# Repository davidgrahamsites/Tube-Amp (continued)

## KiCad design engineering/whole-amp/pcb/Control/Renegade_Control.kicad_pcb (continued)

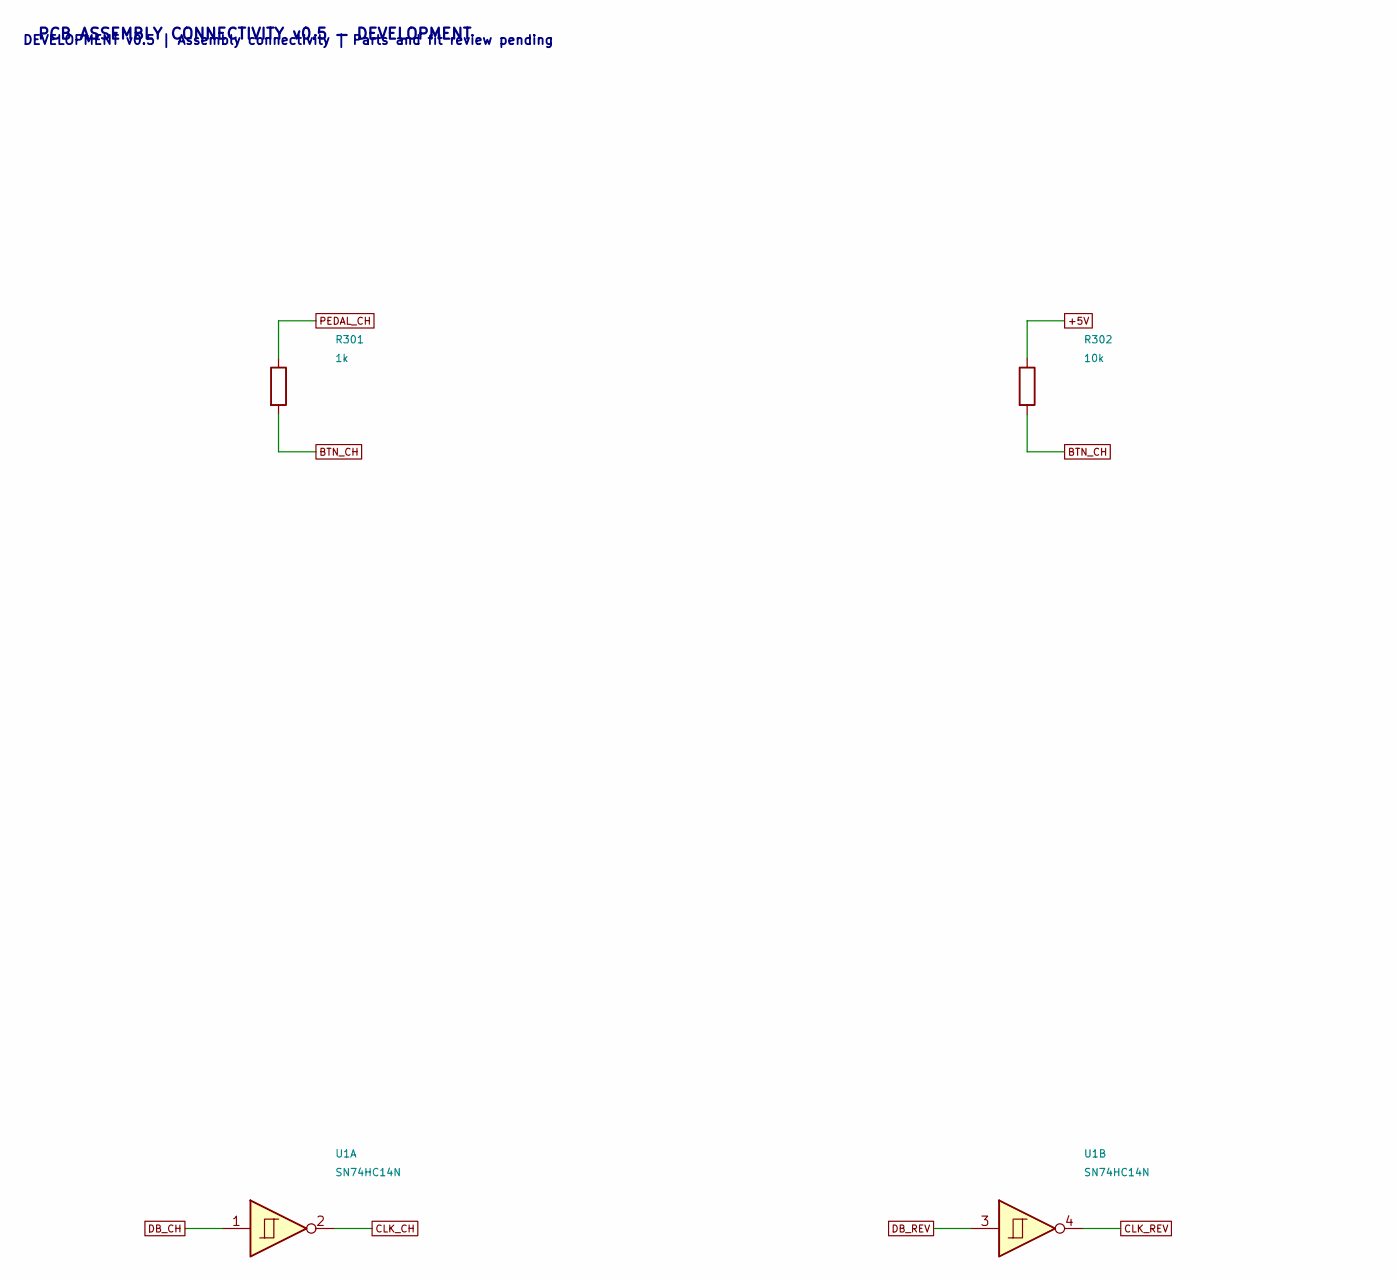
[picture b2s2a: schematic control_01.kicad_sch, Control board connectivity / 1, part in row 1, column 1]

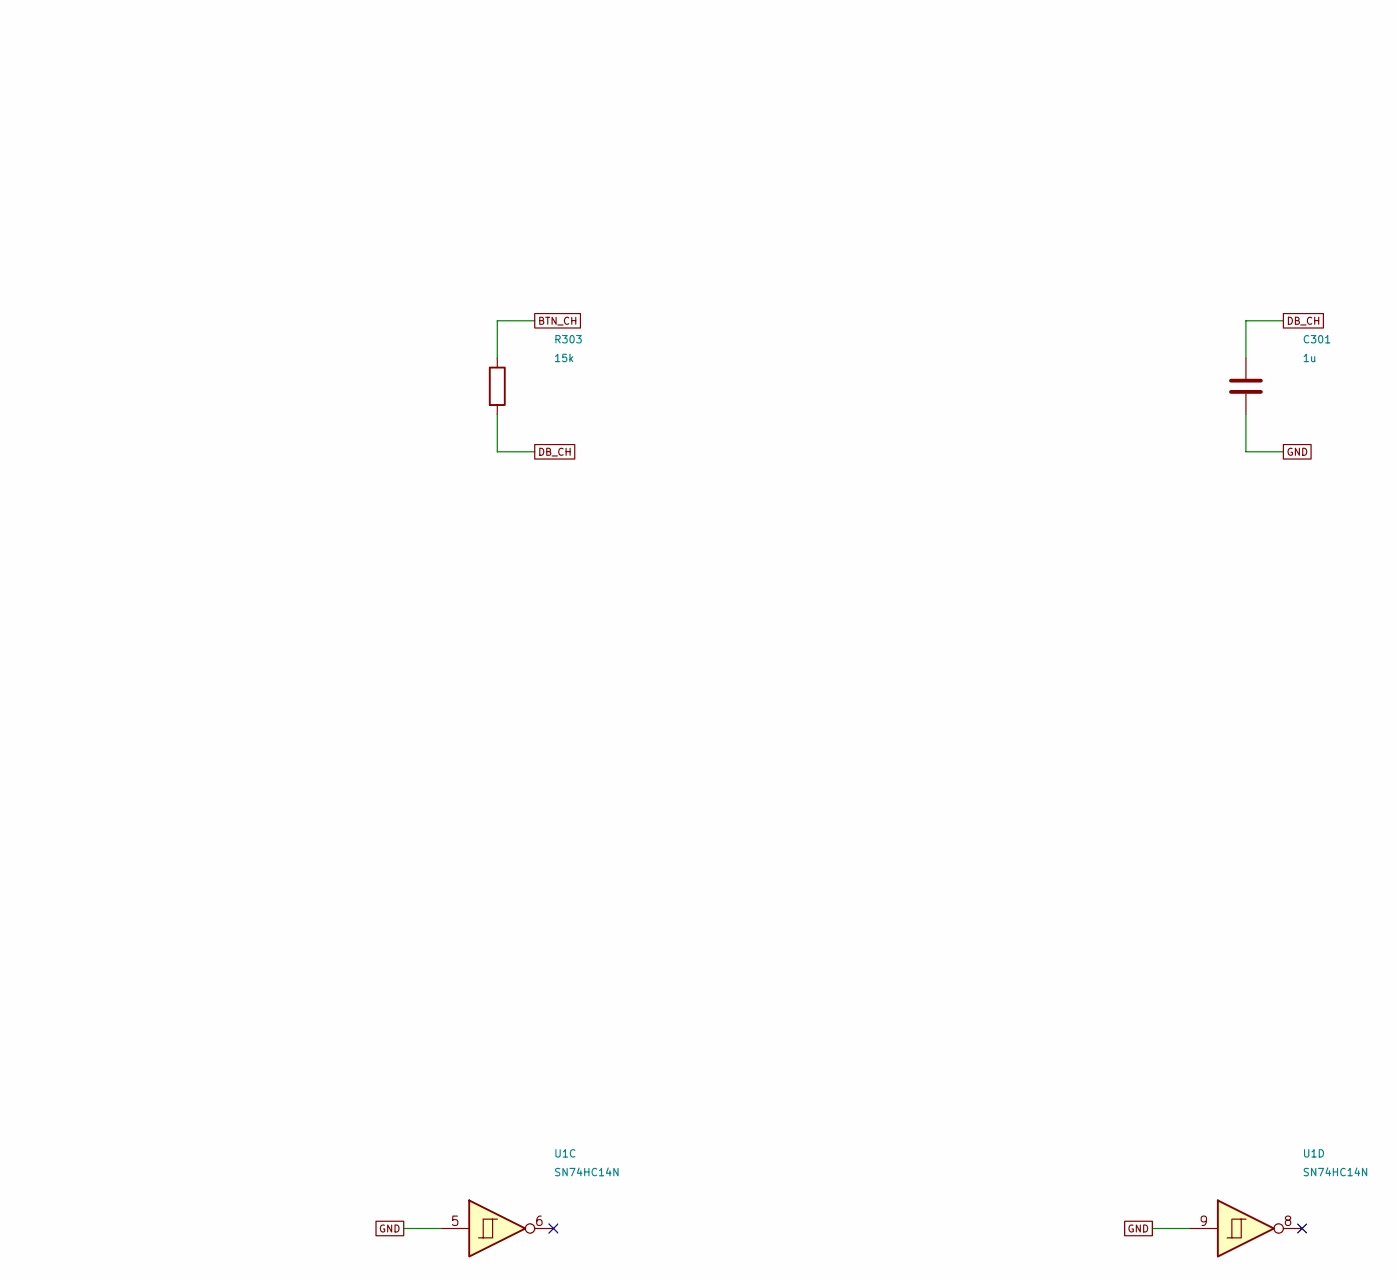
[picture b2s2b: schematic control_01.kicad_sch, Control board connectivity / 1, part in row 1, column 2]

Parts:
C301: 1u; CP_Radial_D8.0mm_P3.50mm; Rating 16 V; effective capacitance/tolerance p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
R301: 1k; R_Axial_DIN0207_L6.3mm_D2.5mm_P10.16mm_Horizontal; Rating 0.25 W; cable current limiter
R302: 10k; R_Axial_DIN0207_L6.3mm_D2.5mm_P10.16mm_Horizontal; Rating 0.25 W
R303: 15k; R_Axial_DIN0207_L6.3mm_D2.5mm_P10.16mm_Horizontal; Rating 1% 0.25 W
U1: SN74HC14N; DIP-14_W7.62mm

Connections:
+5V: R302.1; also elsewhere on the board
BTN_CH: R301.2, R302.2, R303.1; also elsewhere on the board
CLK_CH: U1.2; also elsewhere on the board
CLK_REV: U1.4; also elsewhere on the board
DB_CH: C301.1, R303.2, U1.1
DB_REV: U1.3; also elsewhere on the board
GND: C301.2, U1.5, U1.9; also elsewhere on the board
PEDAL_CH: R301.1; also elsewhere on the board

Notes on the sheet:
PCB ASSEMBLY CONNECTIVITY v0.5 — DEVELOPMENT
DEVELOPMENT v0.5 | Assembly connectivity | Parts and fit review pending

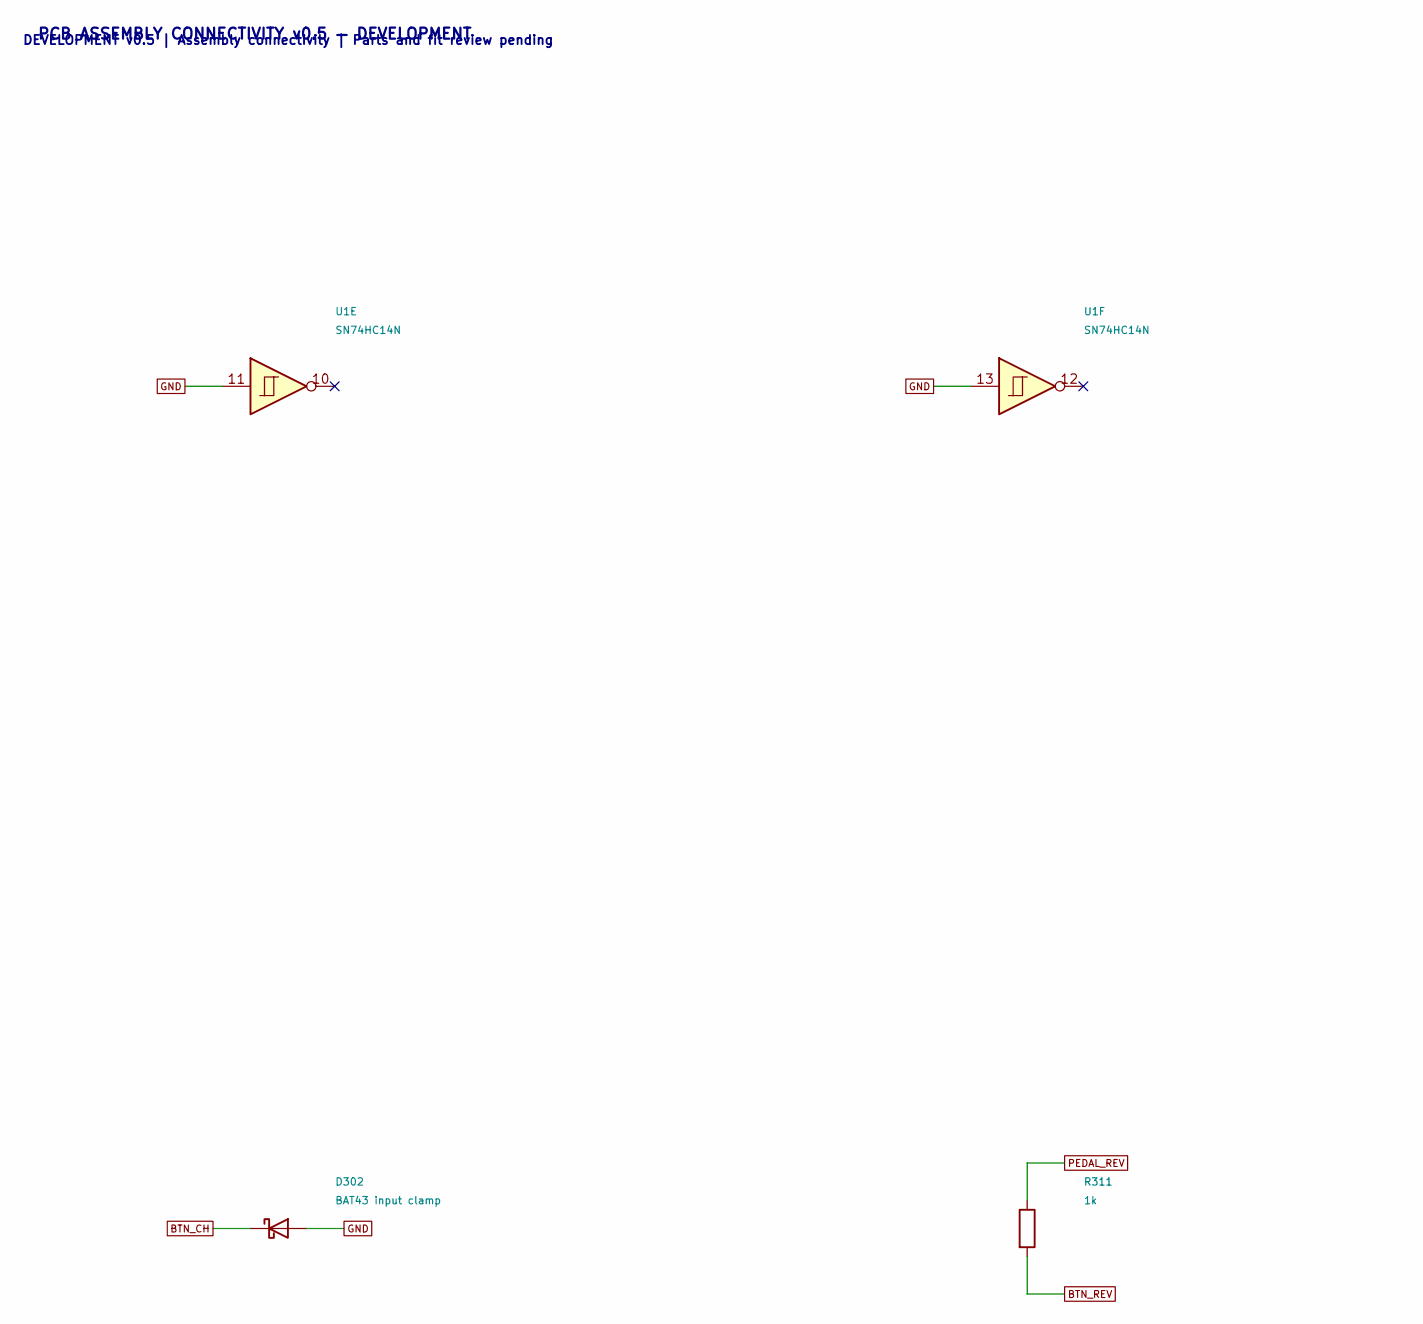
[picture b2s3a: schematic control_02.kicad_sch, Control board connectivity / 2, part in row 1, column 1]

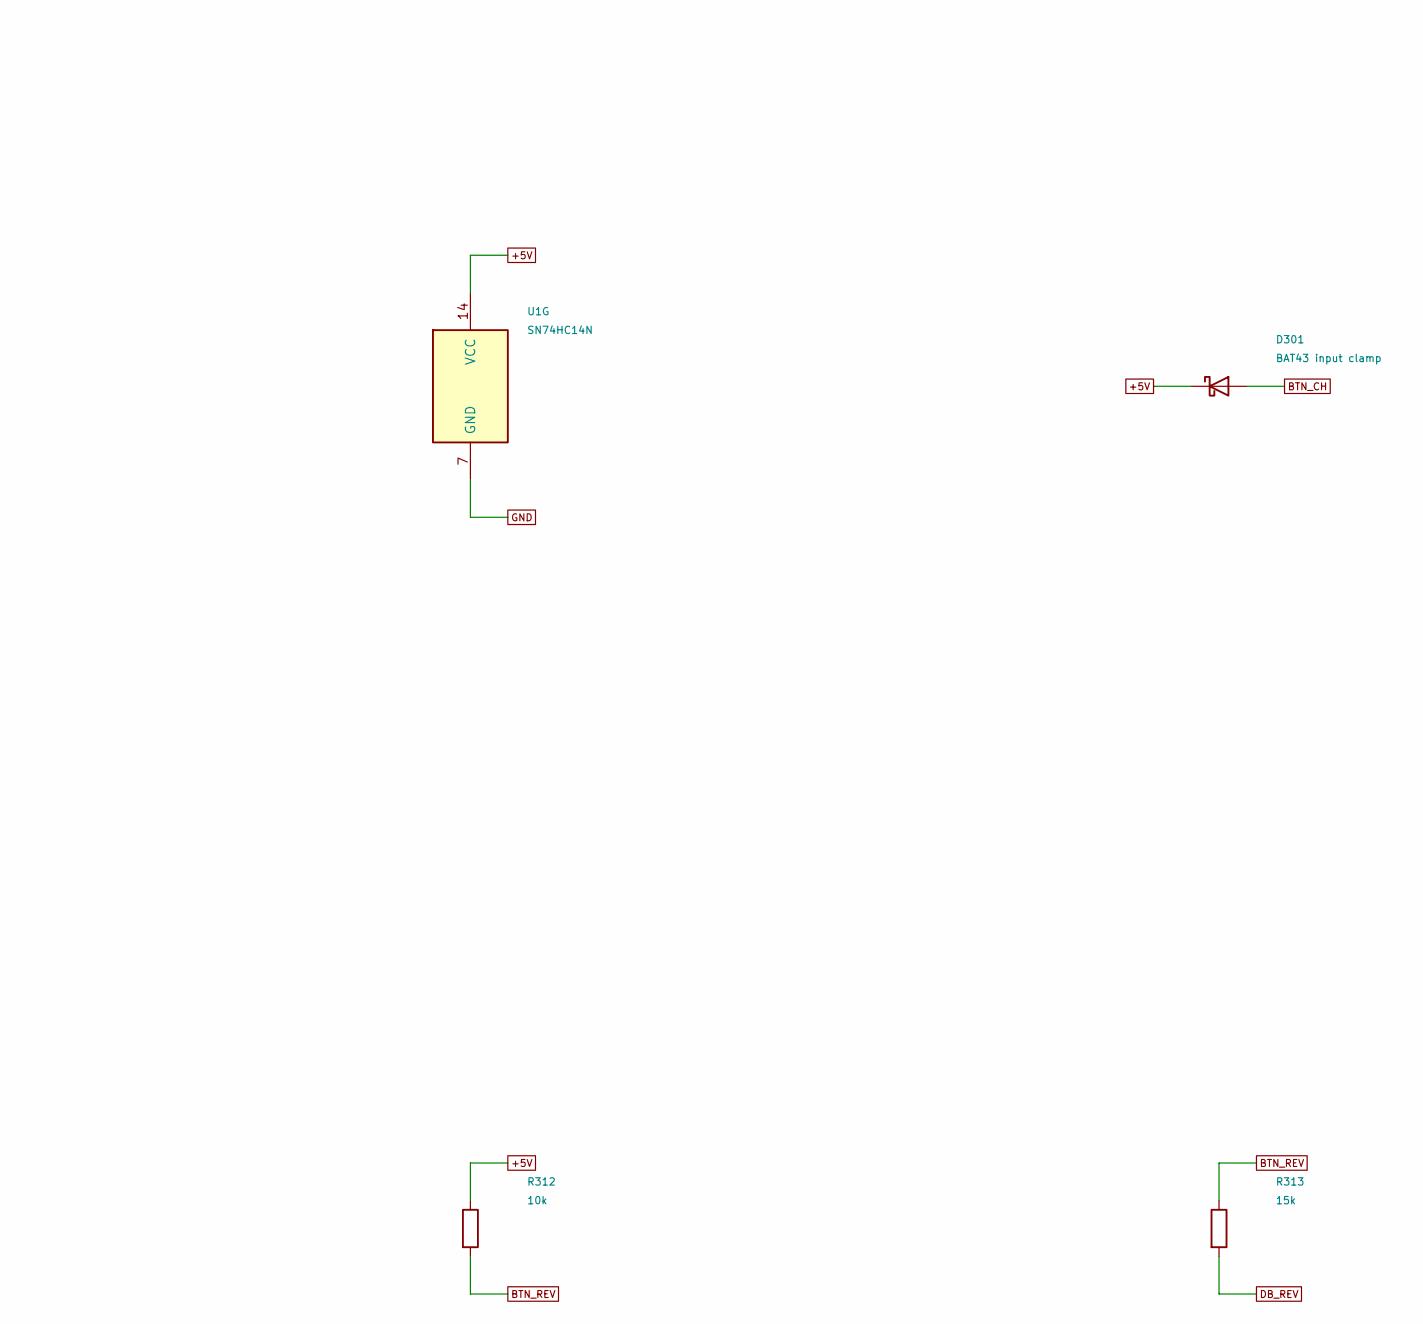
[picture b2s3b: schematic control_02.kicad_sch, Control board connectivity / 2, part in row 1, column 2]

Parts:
D301, D302: BAT43 input clamp; D_DO-35_SOD27_P10.16mm_Horizontal; Rating ESD TVS/connector shell termination sti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
R311: 1k; R_Axial_DIN0207_L6.3mm_D2.5mm_P10.16mm_Horizontal; Rating 0.25 W; cable current limiter
R312: 10k; R_Axial_DIN0207_L6.3mm_D2.5mm_P10.16mm_Horizontal; Rating 0.25 W
R313: 15k; R_Axial_DIN0207_L6.3mm_D2.5mm_P10.16mm_Horizontal; Rating 1% 0.25 W
U1: SN74HC14N; DIP-14_W7.62mm

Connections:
+5V: D301.1 (K), R312.1, U1.14 (VCC); also elsewhere on the board
BTN_CH: D301.2 (A), D302.1 (K); also elsewhere on the board
BTN_REV: R311.2, R312.2, R313.1; also elsewhere on the board
DB_REV: R313.2; also elsewhere on the board
GND: D302.2 (A), U1.7 (GND), U1.11, U1.13; also elsewhere on the board
PEDAL_REV: R311.1; also elsewhere on the board

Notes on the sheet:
PCB ASSEMBLY CONNECTIVITY v0.5 — DEVELOPMENT
DEVELOPMENT v0.5 | Assembly connectivity | Parts and fit review pending

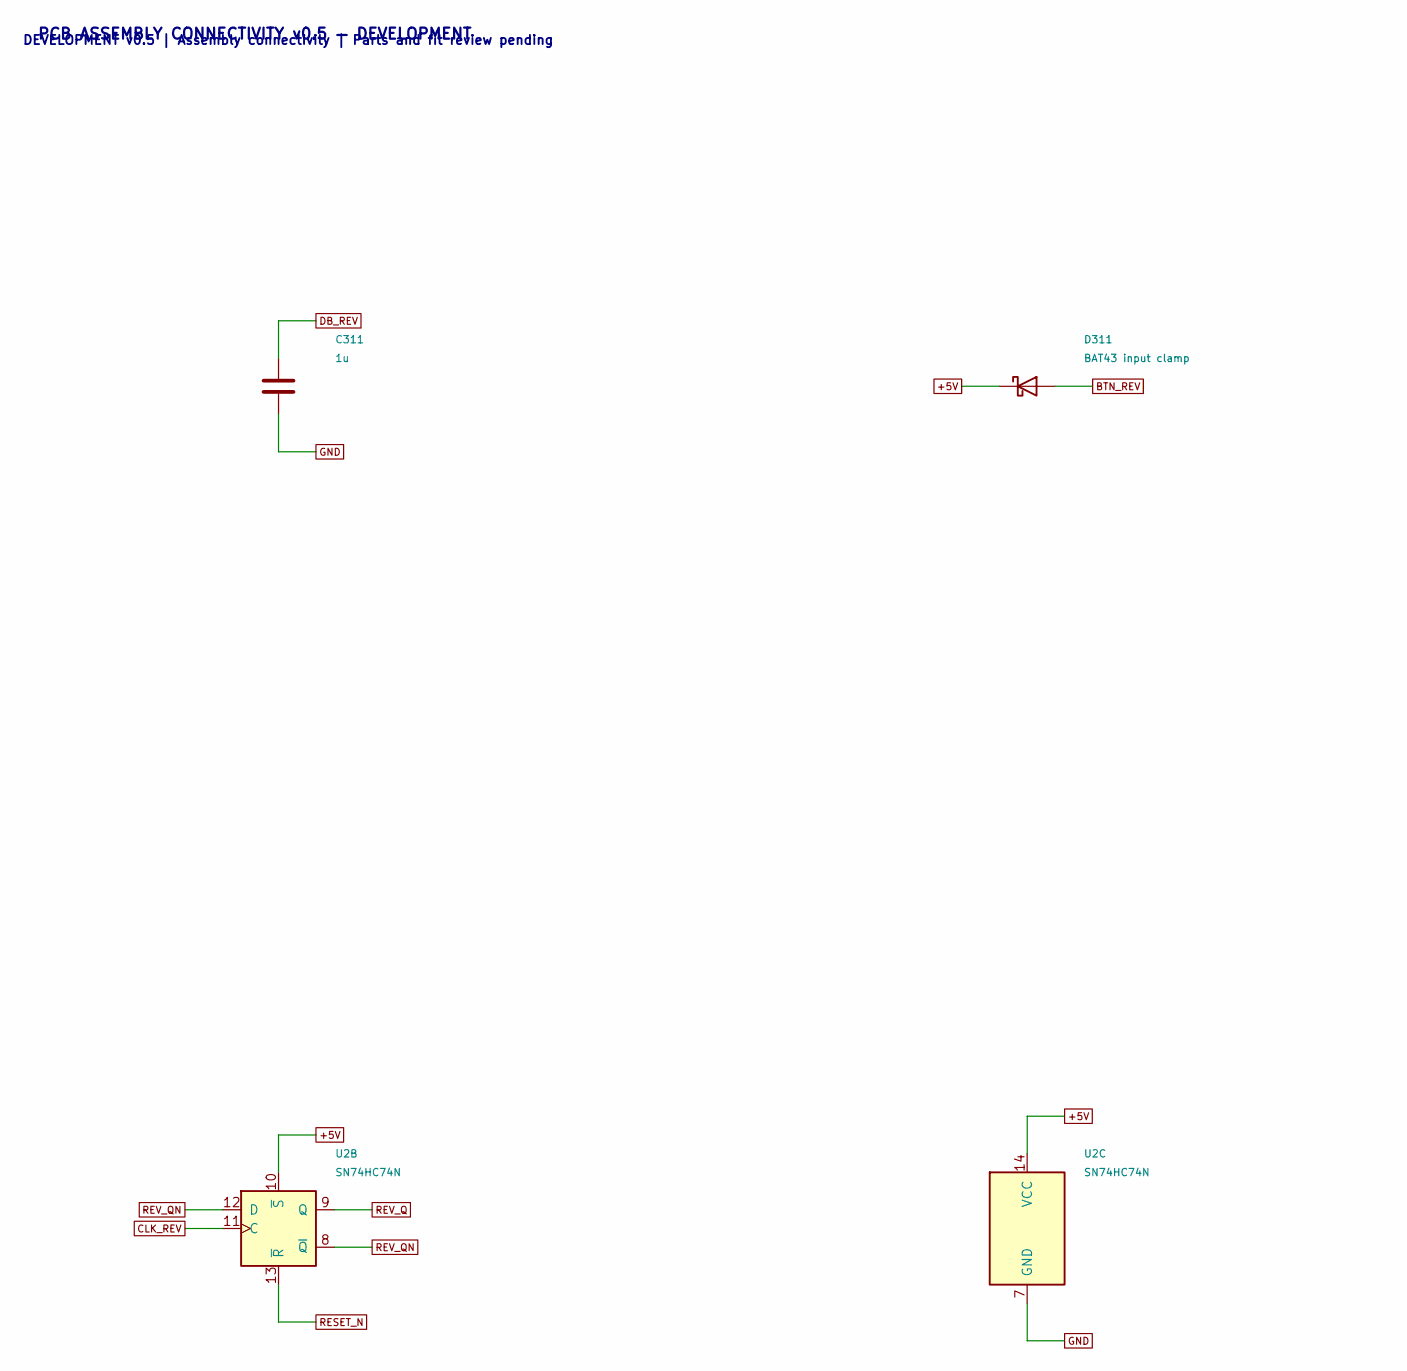
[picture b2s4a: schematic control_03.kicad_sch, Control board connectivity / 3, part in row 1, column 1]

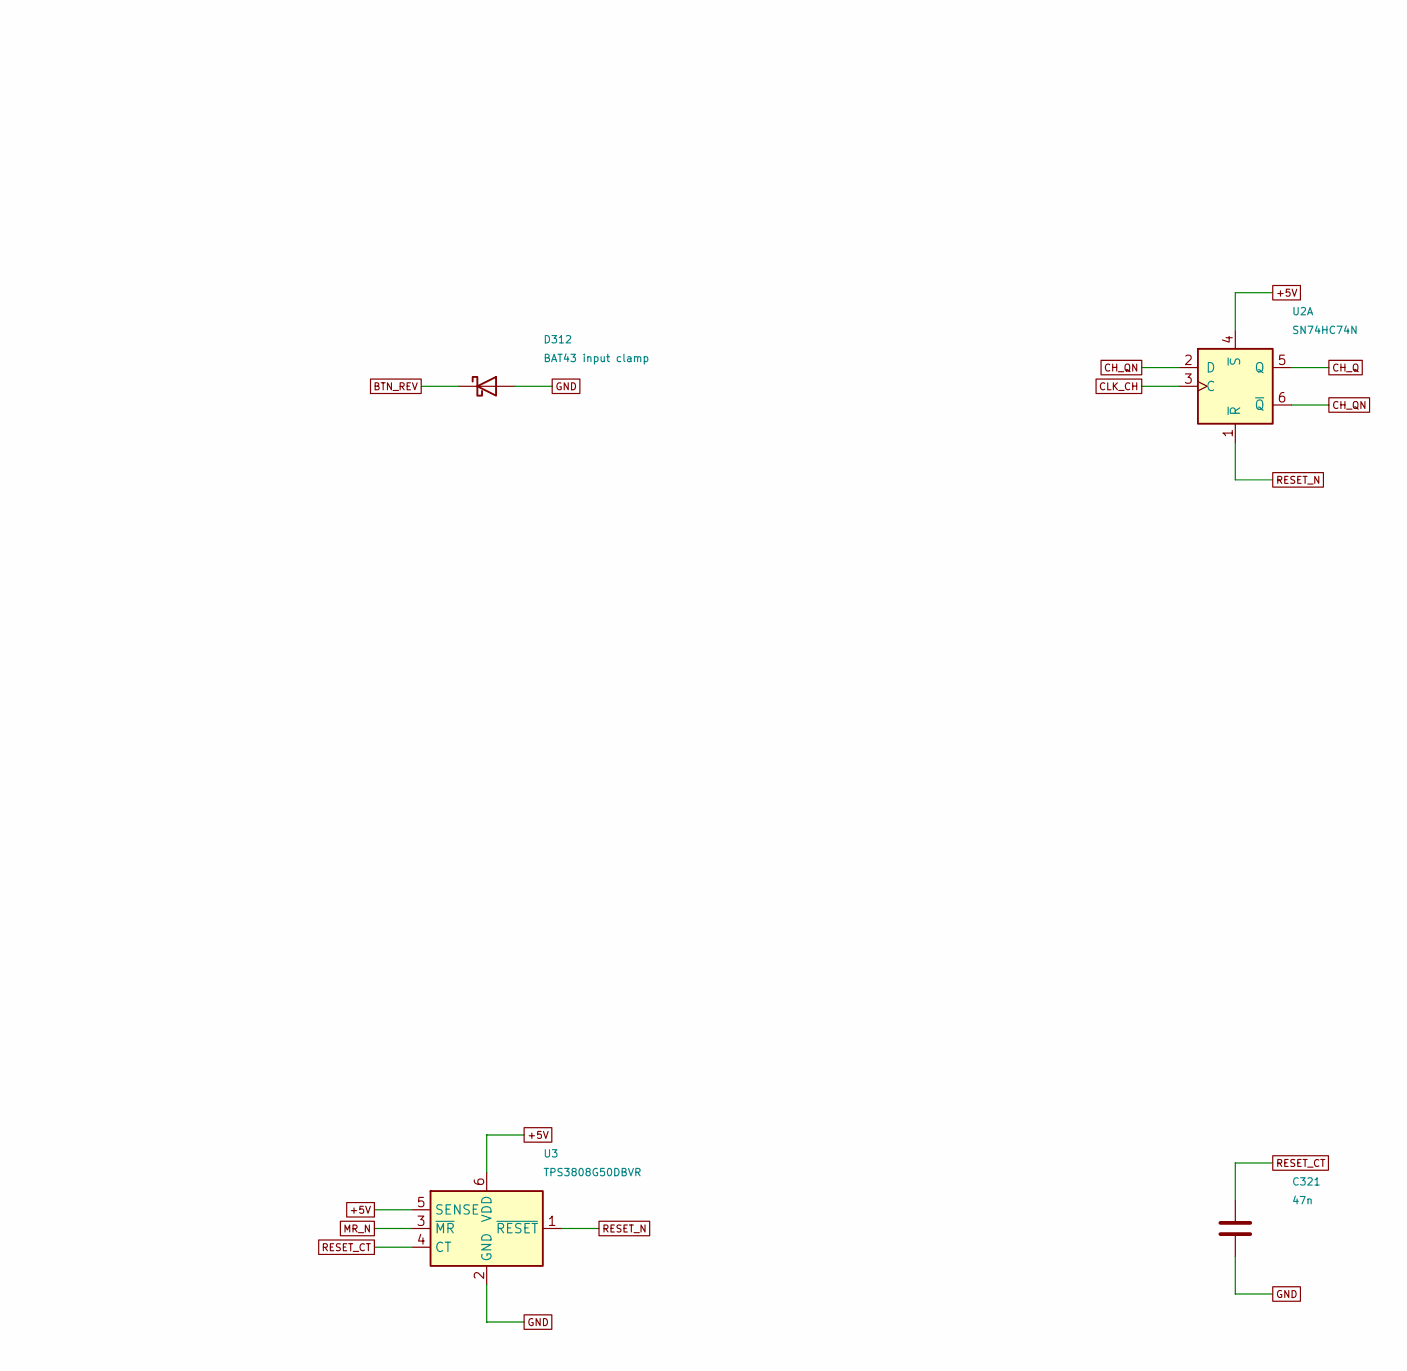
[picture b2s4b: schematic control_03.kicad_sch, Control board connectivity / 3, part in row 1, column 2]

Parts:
C311: 1u; CP_Radial_D8.0mm_P3.50mm; Rating 16 V; effective capacitance/tolerance p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
C321: 47n; C_Rect_L7.2mm_W3.5mm_P5.00mm; Rating 16 V
D311, D312: BAT43 input clamp; D_DO-35_SOD27_P10.16mm_Horizontal; Rating ESD TVS/connector shell termination sti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
U2: SN74HC74N; DIP-14_W7.62mm
U3: TPS3808G50DBVR; SOT-23-6; Rating 4.65V sense; CT timing value subject to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

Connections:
+5V: D311.1 (K), U2.4 (~S), U2.10 (~S), U2.14 (VCC), U3.5 (SENSE), U3.6 (VDD); also elsewhere on the board
BTN_REV: D311.2 (A), D312.1 (K); also elsewhere on the board
CH_Q: U2.5 (Q); also elsewhere on the board
CH_QN: U2.2 (D), U2.6 (~Q)
CLK_CH: U2.3 (C); also elsewhere on the board
CLK_REV: U2.11 (C); also elsewhere on the board
DB_REV: C311.1; also elsewhere on the board
GND: C311.2, C321.2, D312.2 (A), U2.7 (GND), U3.2 (GND); also elsewhere on the board
MR_N: U3.3 (~MR); also elsewhere on the board
RESET_CT: C321.1, U3.4 (CT)
RESET_N: U2.1 (~R), U2.13 (~R), U3.1 (~RESET); also elsewhere on the board
REV_Q: U2.9 (Q); also elsewhere on the board
REV_QN: U2.8 (~Q), U2.12 (D)

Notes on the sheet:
PCB ASSEMBLY CONNECTIVITY v0.5 — DEVELOPMENT
DEVELOPMENT v0.5 | Assembly connectivity | Parts and fit review pending

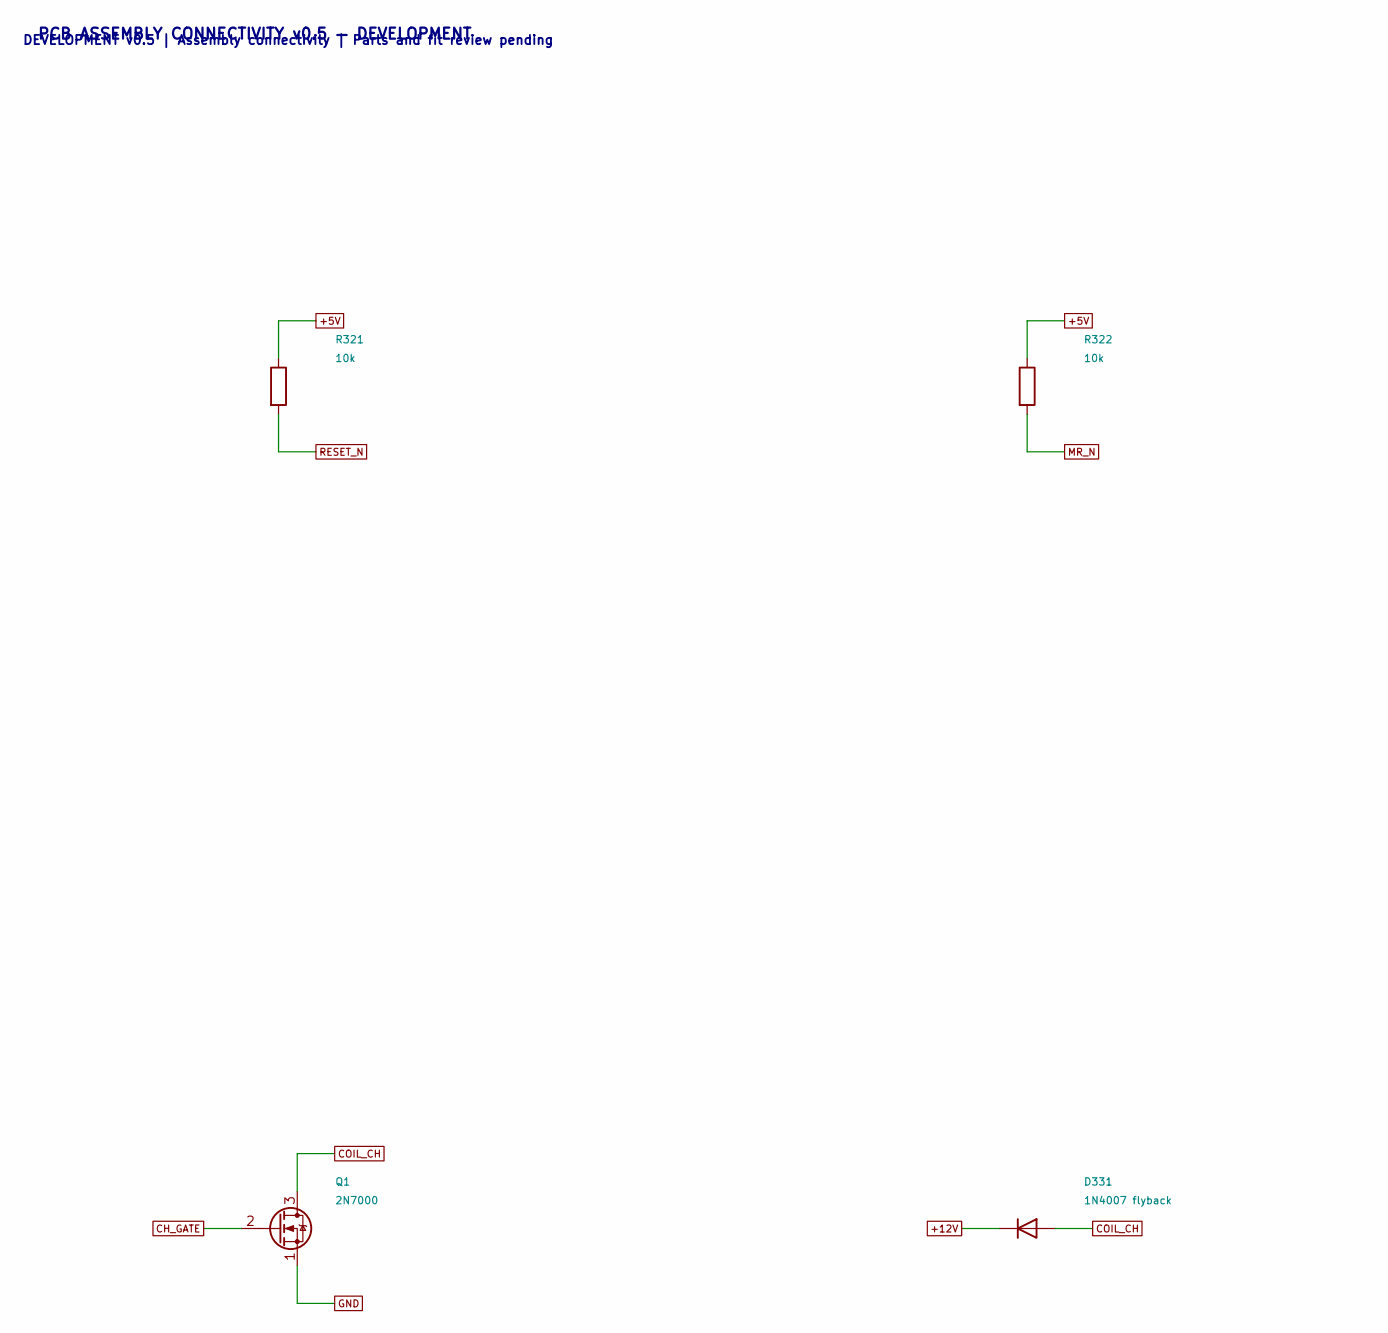
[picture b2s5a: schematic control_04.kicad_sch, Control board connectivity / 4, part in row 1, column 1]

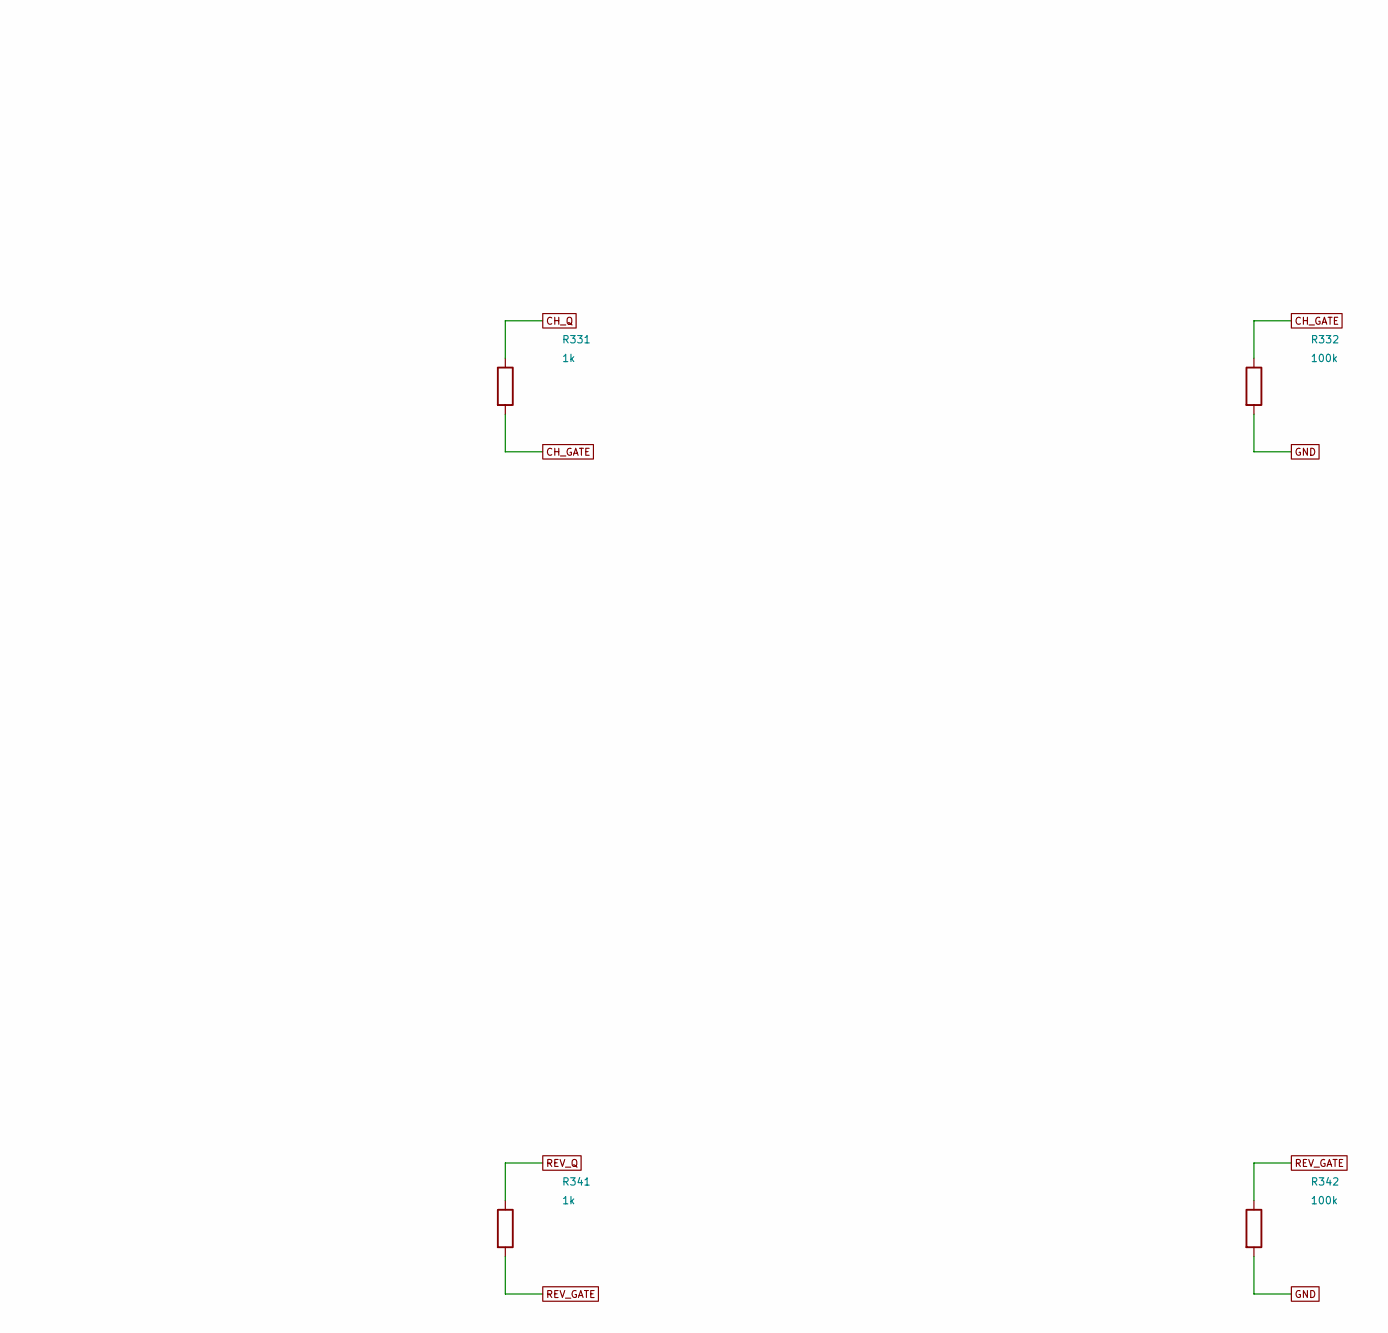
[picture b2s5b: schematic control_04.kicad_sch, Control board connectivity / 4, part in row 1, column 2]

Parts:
D331: 1N4007 flyback; D_DO-41_SOD81_P10.16mm_Horizontal
Q1: 2N7000; TO-92_Inline_Wide; Rating 60 V; verify coil drain transient and g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
R321, R322: 10k; R_Axial_DIN0207_L6.3mm_D2.5mm_P10.16mm_Horizontal; Rating 0.25 W
R331, R341: 1k; R_Axial_DIN0207_L6.3mm_D2.5mm_P10.16mm_Horizontal; Rating 0.25 W
R332, R342: 100k; R_Axial_DIN0207_L6.3mm_D2.5mm_P10.16mm_Horizontal; Rating 0.25 W

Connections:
+5V: R321.1, R322.1; also elsewhere on the board
+12V: D331.1 (K); also elsewhere on the board
CH_GATE: Q1.2 (G), R331.2, R332.1
CH_Q: R331.1; also elsewhere on the board
COIL_CH: D331.2 (A), Q1.3 (D); also elsewhere on the board
GND: Q1.1 (S), R332.2, R342.2; also elsewhere on the board
MR_N: R322.2; also elsewhere on the board
RESET_N: R321.2; also elsewhere on the board
REV_GATE: R341.2, R342.1; also elsewhere on the board
REV_Q: R341.1; also elsewhere on the board

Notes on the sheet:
PCB ASSEMBLY CONNECTIVITY v0.5 — DEVELOPMENT
DEVELOPMENT v0.5 | Assembly connectivity | Parts and fit review pending

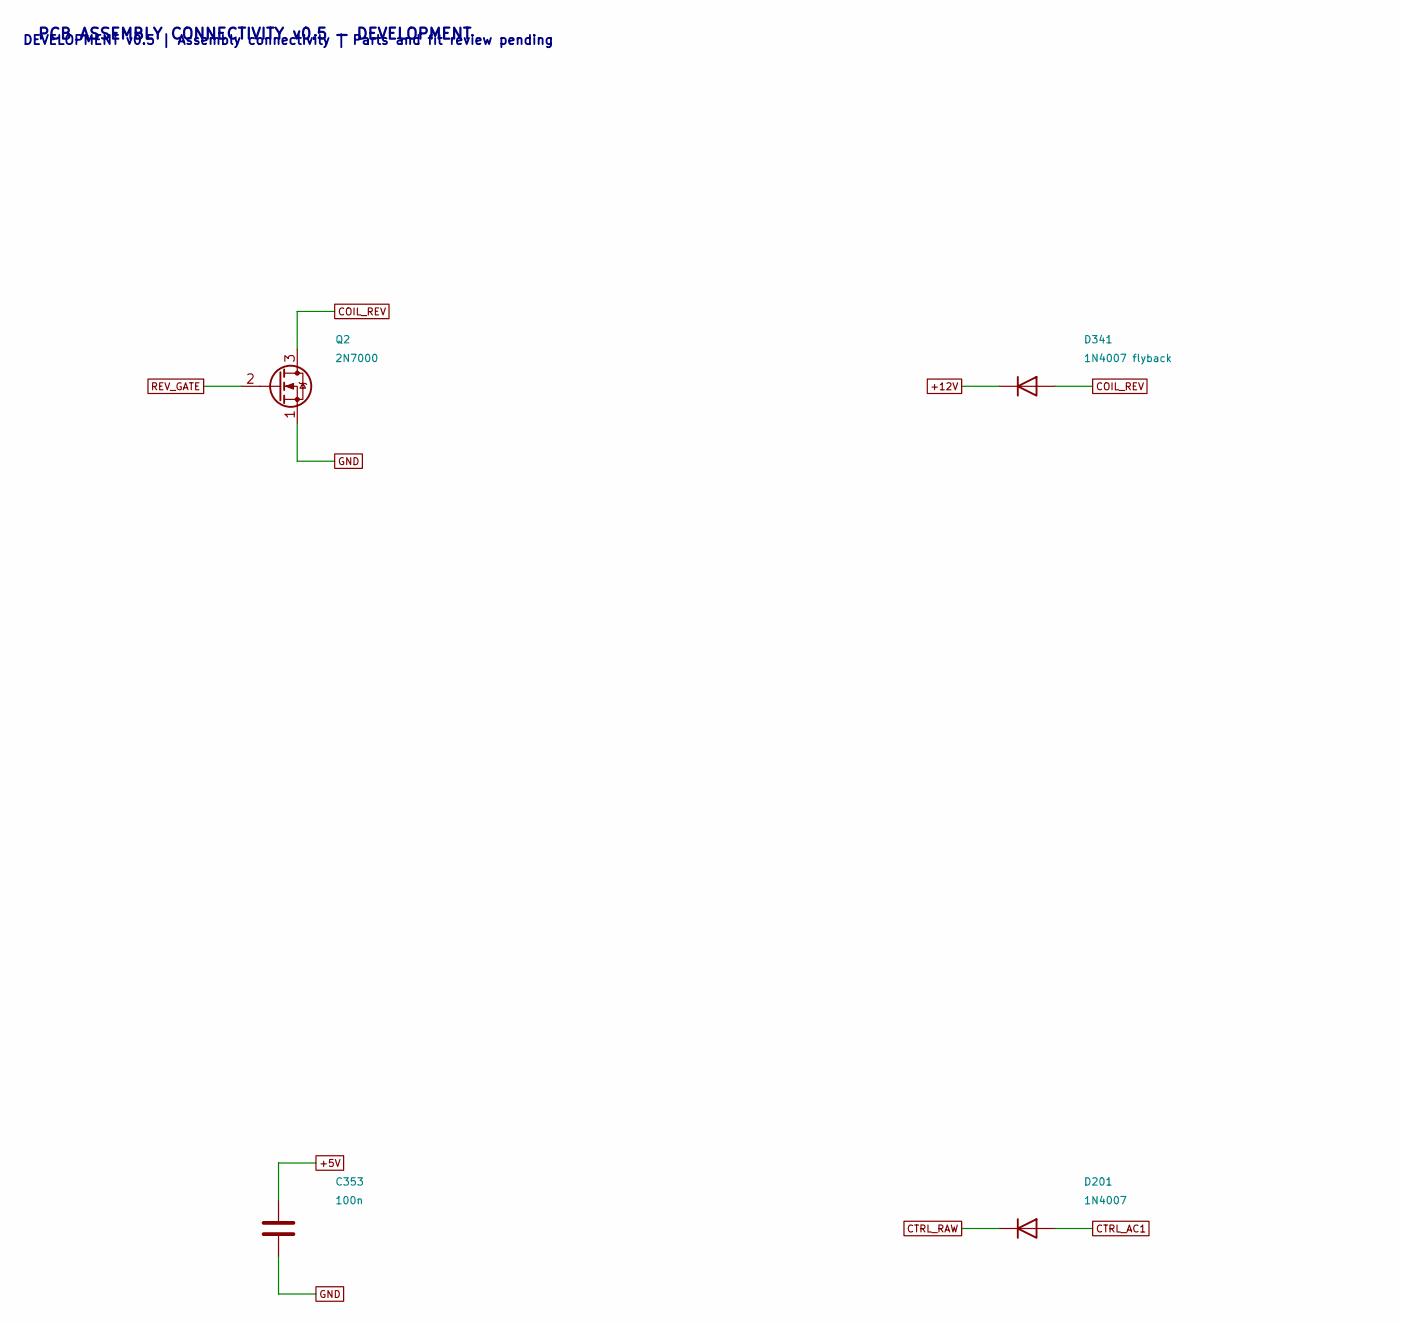
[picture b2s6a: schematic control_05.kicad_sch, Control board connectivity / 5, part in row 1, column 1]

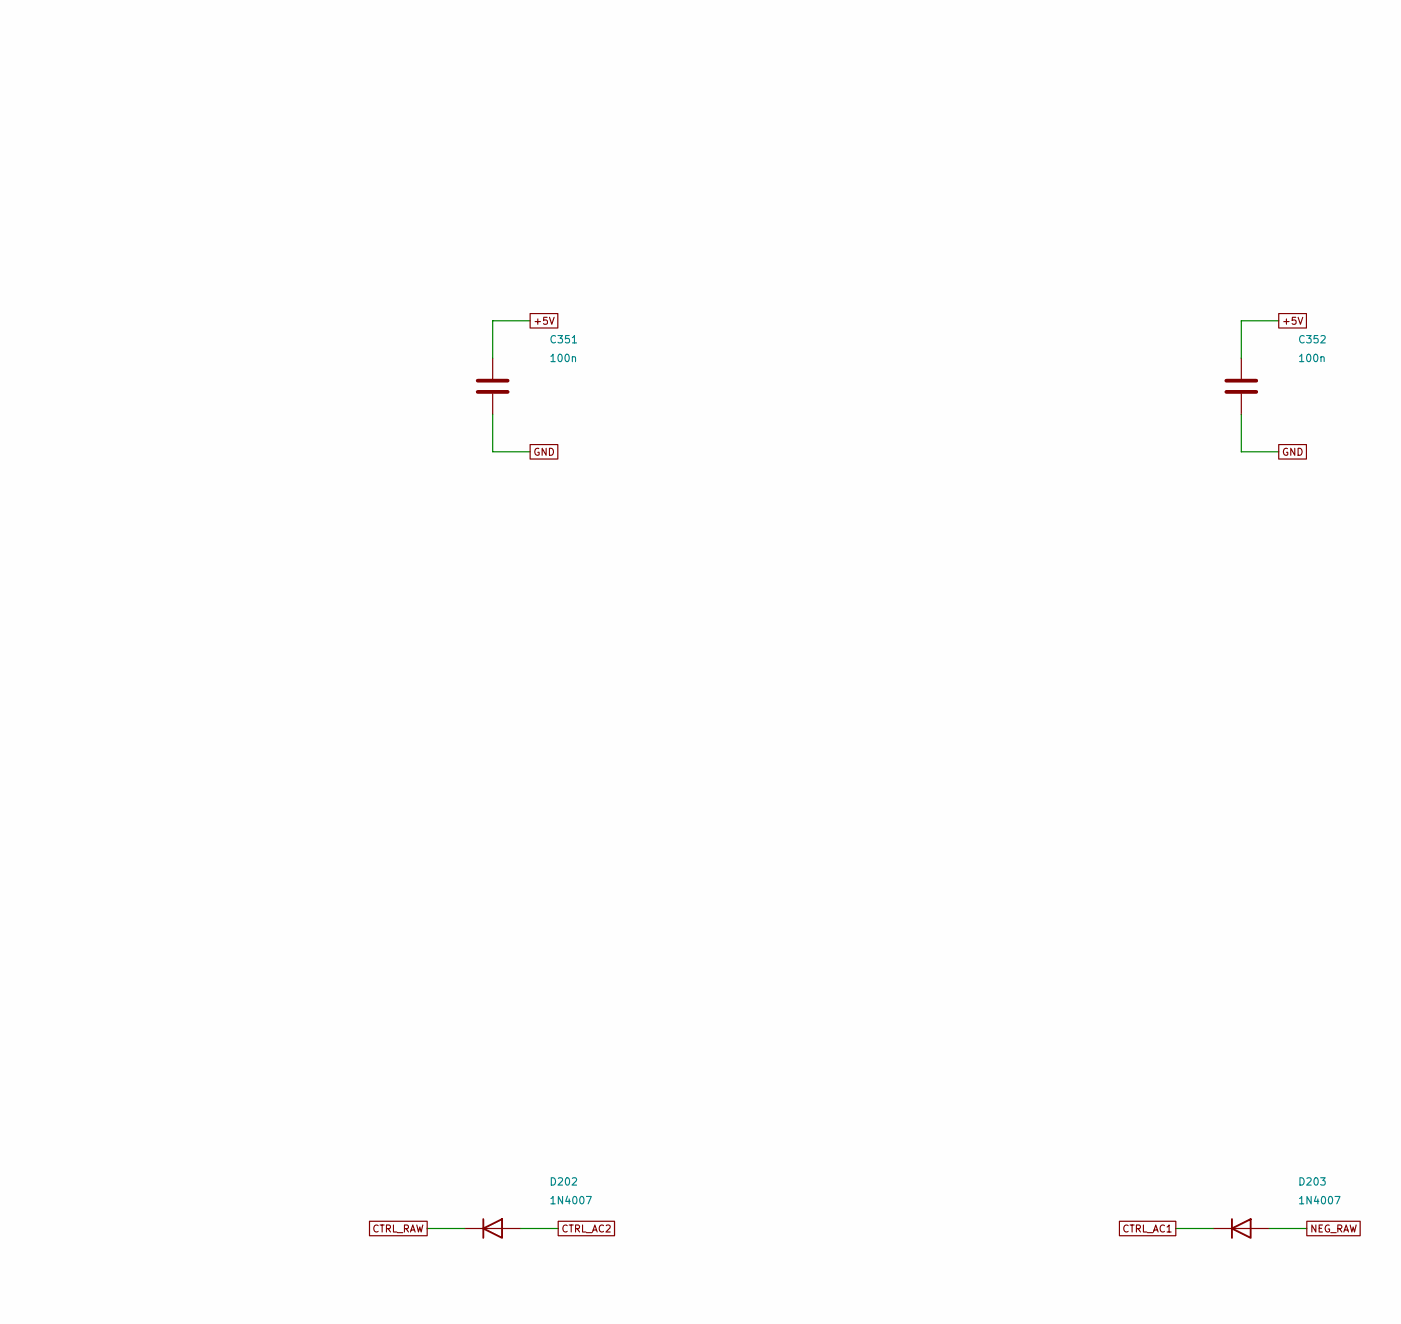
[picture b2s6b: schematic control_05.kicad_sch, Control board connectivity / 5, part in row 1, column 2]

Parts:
C351, C352, C353: 100n; C_Rect_L7.2mm_W3.5mm_P5.00mm; Rating 16 V; one at each IC
D201, D202, D203: 1N4007; D_DO-41_SOD81_P10.16mm_Horizontal
D341: 1N4007 flyback; D_DO-41_SOD81_P10.16mm_Horizontal
Q2: 2N7000; TO-92_Inline_Wide; Rating 60 V; verify coil drain transient and g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

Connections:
+5V: C351.1, C352.1, C353.1; also elsewhere on the board
+12V: D341.1 (K); also elsewhere on the board
COIL_REV: D341.2 (A), Q2.3 (D); also elsewhere on the board
CTRL_AC1: D201.2 (A), D203.1 (K); also elsewhere on the board
CTRL_AC2: D202.2 (A); also elsewhere on the board
CTRL_RAW: D201.1 (K), D202.1 (K); also elsewhere on the board
GND: C351.2, C352.2, C353.2, Q2.1 (S); also elsewhere on the board
NEG_RAW: D203.2 (A); also elsewhere on the board
REV_GATE: Q2.2 (G); also elsewhere on the board

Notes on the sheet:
PCB ASSEMBLY CONNECTIVITY v0.5 — DEVELOPMENT
DEVELOPMENT v0.5 | Assembly connectivity | Parts and fit review pending
